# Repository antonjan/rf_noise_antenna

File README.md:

# rf_noise_antenna
This repository will have all the details for the active antenna board for Rasdpberry PI<br>
This project will have the Raspberry Pi HAT that will switch in the LOW and HIGH pass filters depending on IO-PIN4 on raspberry Pi.<br>
What is still missing from this project is the actual active antenna.<br>
<b>RF Noise Block Diagram</b><br>
<br>
There is also a Isolation transformer on the board to eliminate the DC ground from the antenna and generating noise.<br>
This antenna consists of a raspberry HAT for RF filter and power injection for the active Antenna.<br>
<br>
# Project Status
This Project is Now Compleet. (The PCB Board still needs to be build and Tested)<br>
# Live Monitoring system
<a href="http://rfnoise.amsatsa.org.za/">http://rfnoise.amsatsa.org.za/</a><br>
# More Documentation
<a href="https://github.com/antonjan/rf_noise_antenna/tree/master/doc">More Dokuments click here</a><br>
<b>Diagram of Active antenna base filter.</b><br>
<br><br>
PCB Layout<br>
<br><br>
<b>PCB Layout</b><br>
<br><br>
<b>PCB Layout 3D</b><br>
<br><br>
<b>Filter Low PASS</b><br>
<br><br>
<b>Filter High PASS</b><br>
<br><br>
<br>

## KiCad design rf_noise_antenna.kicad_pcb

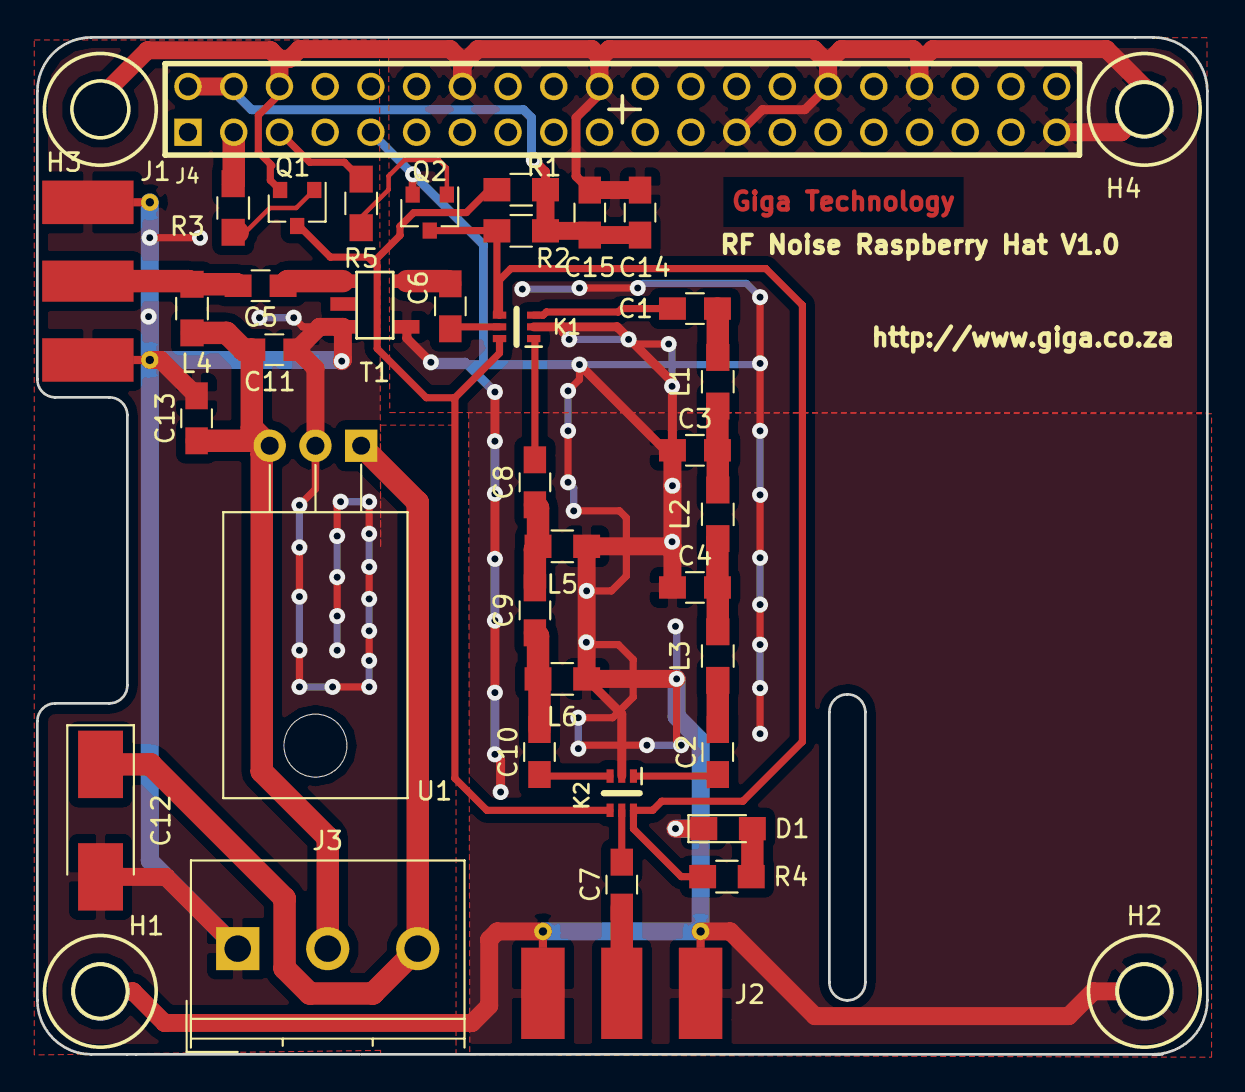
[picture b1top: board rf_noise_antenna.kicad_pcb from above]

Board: 2 copper layers, 65.0 x 56.5 mm, 41 parts (0 on the bottom side), 28 nets.

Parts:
C1, C2, C5, C6, C7, C11, C14: 100nF; C_0805_HandSoldering
C3, C4: 360pF; C_0805_HandSoldering
C8, C10: 390pF; C_0805_HandSoldering
C9: 120pF; C_0805_HandSoldering
C12: 47uF 16V; CP_Tantalum_Case-C_EIA-6032-28_Hand
C13, C15: 4.7uF 16V; C_0805_HandSoldering
D1: LED; LED_0805_HandSoldering
H1, H2, H3, H4: Conn_01x01; MountingHole_3.2mm_M3
J1, J2: Conn_Coaxial; Molex_SMA_Jack_Edge_Mount
J3: Conn_01x03; TerminalBlock_Philmore_TB133_03x5mm_Straight
J4: Raspberry_Pi_2_3; PIN_ARRAY_20X2
K1, K2: MASWSS0115; SC-70-6
L1, L3: 330nH; L_0805_HandSoldering
L2: 1.1uH; L_0805_HandSoldering
L4: 1mH; L_0805_HandSoldering
L5, L6: 360nH; L_0805_HandSoldering
Q1, Q2: BC847; SOT-23
R1, R2, R4: 250; R_0805_HandSoldering
R3, R5: 1k2; R_0805_HandSoldering
T1: MABA-009180-500MHz_1P_1S; SM22
U1: L7809; TO-220_Horizontal

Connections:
+5V: C14.1, C15.1, J4.2, J4.4, R1.2, R2.2
GND: C3.1, C4.1, C14.2, C15.2, D1.1, H1.1, H2.1, H3.1, H4.1, J2.2, J4.6, J4.9, J4.14, J4.20, J4.25, J4.30, J4.34, J4.39, K1.2, K2.2, L5.1, L6.1, Q1.2, Q2.2, T1.4
GNDA: C11.2, C12.2, C13.2, J1.2, J3.1, T1.3, U1.2
unnamed: C1.1, L1.2
unnamed: C1.2, K1.3
unnamed: C2.1, K2.1
unnamed: C2.2, L3.1
unnamed: C3.2, L1.1, L2.2
unnamed: C4.2, L2.1, L3.2
unnamed: C5.1, T1.1
unnamed: C5.2, J1.1, L4.1
unnamed: C6.1, K1.5
unnamed: C6.2, T1.5
unnamed: C7.1, J2.1
unnamed: C7.2, K2.5
unnamed: C8.1, C9.2, L5.2
unnamed: C8.2, K1.1
unnamed: C10.1, K2.3
unnamed: C9.1, C10.2, L6.2
unnamed: C11.1, C13.1, J3.2, L4.2, U1.3
unnamed: C12.1, J3.3, U1.1
unnamed: D1.2, R4.1
unnamed: J4.3, R3.1
unnamed: J4.5, R5.2
unnamed: K1.4, K2.6, Q2.3, R2.1, R4.2
unnamed: K1.6, K2.4, Q1.3, R1.1
unnamed: Q1.1, R3.2
unnamed: Q2.1, R5.1

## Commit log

2018-08-17 Added diagram
2018-08-17 adding com Values
2018-08-17 Change isolation to be at antenna
2018-08-17 Fix DR cherck
2018-08-18 Added filter details
2018-08-18 fix path
2018-08-19 Creating rf relay
2018-08-19 Replace relay with Solit state
2018-08-21 add componet ref
2018-08-22 adding Diagram
2018-08-22 add link to diagram
2018-08-22 change diagram
2018-08-22 update diagram
2018-08-25 Starting with PCB Layout
2018-08-26 Compleet pcb
2018-08-26 Added measurmets
2018-08-26 add diagram
2018-08-26 Fix Transistor pin config
2018-08-26 Add diagram img
2018-08-26 adding filter details
2018-08-26 add details
2018-08-27 fixed transistor
2018-08-27 fix url path
2018-08-27 Fix URL
2018-08-27 fix formatting
2018-08-27 fix format
2018-08-27 adding block diagram
2018-08-27 adding pcb_pic
2018-08-27 add pic
2018-08-27 add 3d view
2018-08-27 Fix LED and Inductor value
2018-08-27 adding more details
2018-08-28 fix spelling
2018-08-29 Added Bom file
2018-08-29 adding Bom details
2018-10-09 added link to docks
2018-10-25 Added active Antenna
2018-10-25 Added anotation for active Antenna
2018-11-06 adding V2 files
2018-11-22 adding anteena swich controle
2018-11-22 add pin direction
2018-11-23 adding readme
